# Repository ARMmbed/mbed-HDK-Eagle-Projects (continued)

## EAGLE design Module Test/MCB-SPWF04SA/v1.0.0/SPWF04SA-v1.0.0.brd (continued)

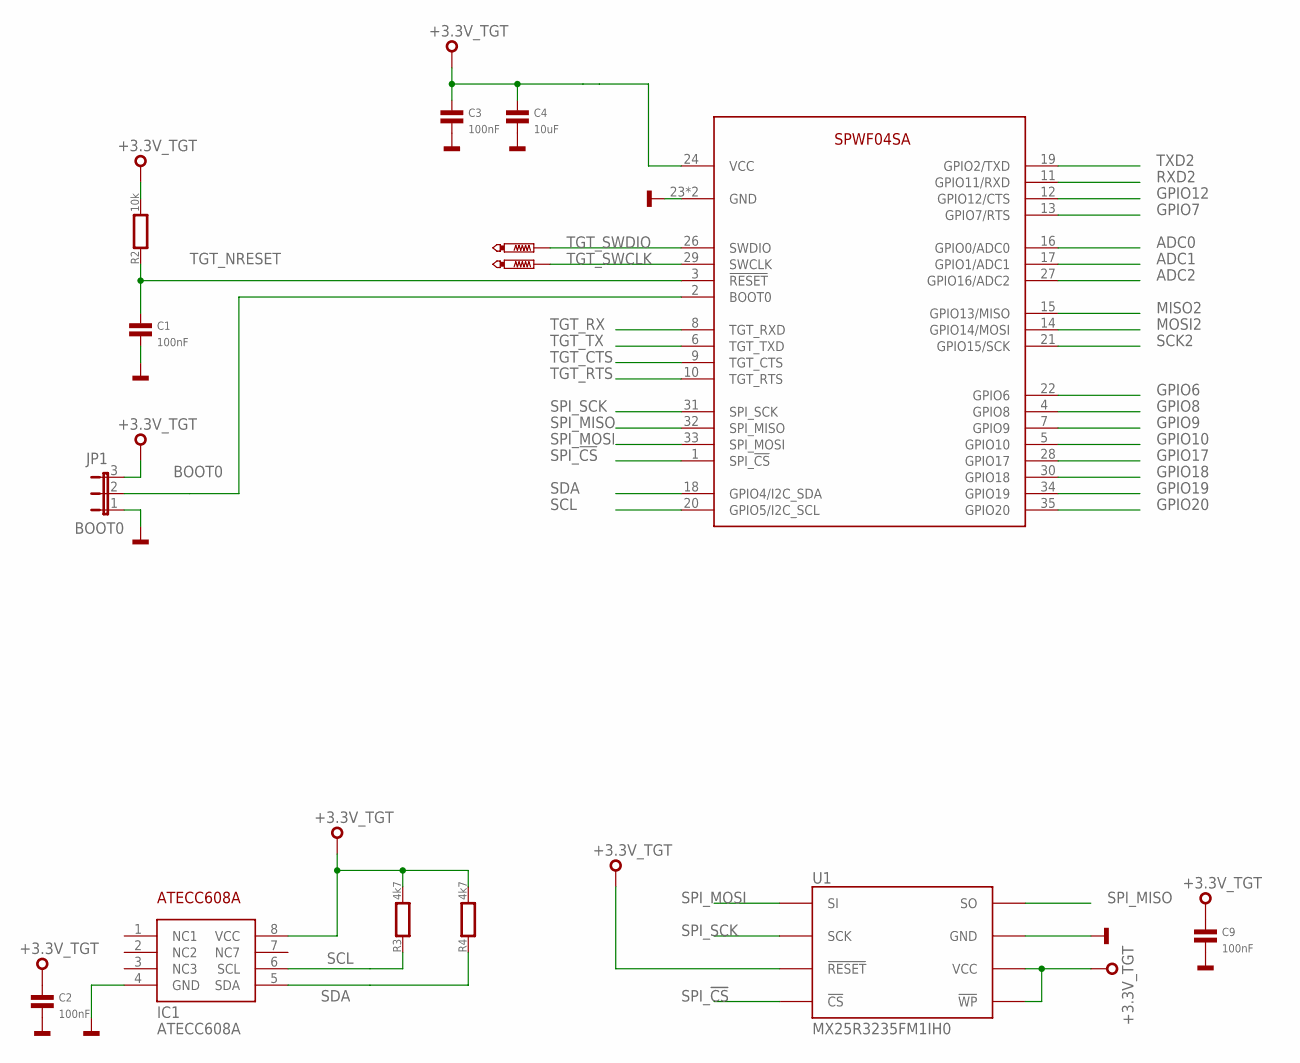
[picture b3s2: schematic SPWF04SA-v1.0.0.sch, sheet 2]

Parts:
C1, C2, C3, C9: 100nF; 0603
C4: 10uF; 0603
IC1: ATECC608A; SO8
JP1: BOOT0; JP2
MOD2: SPWF04SA
R2: 10k; 0603
R3, R4: 4k7; 0603
TP3, TP4: PTR1TP10R; TP10R
U1: MX25R3235FM1IH0; SO8

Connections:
+3.3V_TGT: C2.1, C3.1, C4.1, C9.1, IC1.8 (VCC), JP1.3, MOD2.24 (VCC), R2.2, R3.2, R4.2, U1.3 (!WP), U1.7 (!RESET), U1.8 (VCC); also elsewhere on the board
ADC0: MOD2.16 (GPIO0/ADC0); also elsewhere on the board
ADC1: MOD2.17 (GPIO1/ADC1); also elsewhere on the board
ADC2: MOD2.27 (GPIO16/ADC2); also elsewhere on the board
BOOT0: JP1.2, MOD2.2 (BOOT0)
GND: C1.2, C2.2, C3.2, C4.2, C9.2, IC1.4 (GND), JP1.1, MOD2.23 (GND), MOD2.25 (GND), U1.4 (GND); also elsewhere on the board
GPIO6: MOD2.22 (GPIO6); also elsewhere on the board
GPIO7: MOD2.13 (GPIO7/RTS); also elsewhere on the board
GPIO8: MOD2.4 (GPIO8); also elsewhere on the board
GPIO9: MOD2.7 (GPIO9); also elsewhere on the board
GPIO10: MOD2.5 (GPIO10)
GPIO12: MOD2.12 (GPIO12/CTS); also elsewhere on the board
GPIO17: MOD2.28 (GPIO17)
GPIO18: MOD2.30 (GPIO18); also elsewhere on the board
GPIO19: MOD2.34 (GPIO19)
GPIO20: MOD2.35 (GPIO20); also elsewhere on the board
MISO2: MOD2.15 (GPIO13/MISO); also elsewhere on the board
MOSI2: MOD2.14 (GPIO14/MOSI); also elsewhere on the board
RXD2: MOD2.11 (GPIO11/RXD); also elsewhere on the board
SCK2: MOD2.21 (GPIO15/SCK); also elsewhere on the board
SCL: IC1.6 (SCL), MOD2.20 (GPIO5/I2C_SCL), R3.1; also elsewhere on the board
SDA: IC1.5 (SDA), MOD2.18 (GPIO4/I2C_SDA), R4.1; also elsewhere on the board
SPI_!CS: MOD2.1 (SPI_!CS), U1.1 (!CS)
SPI_MISO: MOD2.32 (SPI_MISO), U1.2 (SO); also elsewhere on the board
SPI_MOSI: MOD2.33 (SPI_MOSI), U1.5 (SI); also elsewhere on the board
SPI_SCK: MOD2.31 (SPI_SCK), U1.6 (SCK); also elsewhere on the board
TGT_CTS: MOD2.9 (TGT_CTS); also elsewhere on the board
TGT_NRESET: C1.1, MOD2.3 (!RESET), R2.1; also elsewhere on the board
TGT_RTS: MOD2.10 (TGT_RTS); also elsewhere on the board
TGT_RX: MOD2.8 (TGT_RXD); also elsewhere on the board
TGT_SWCLK: MOD2.29 (SWCLK), TP4.TP; also elsewhere on the board
TGT_SWDIO: MOD2.26 (SWDIO), TP3.TP; also elsewhere on the board
TGT_TX: MOD2.6 (TGT_TXD); also elsewhere on the board
TXD2: MOD2.19 (GPIO2/TXD); also elsewhere on the board

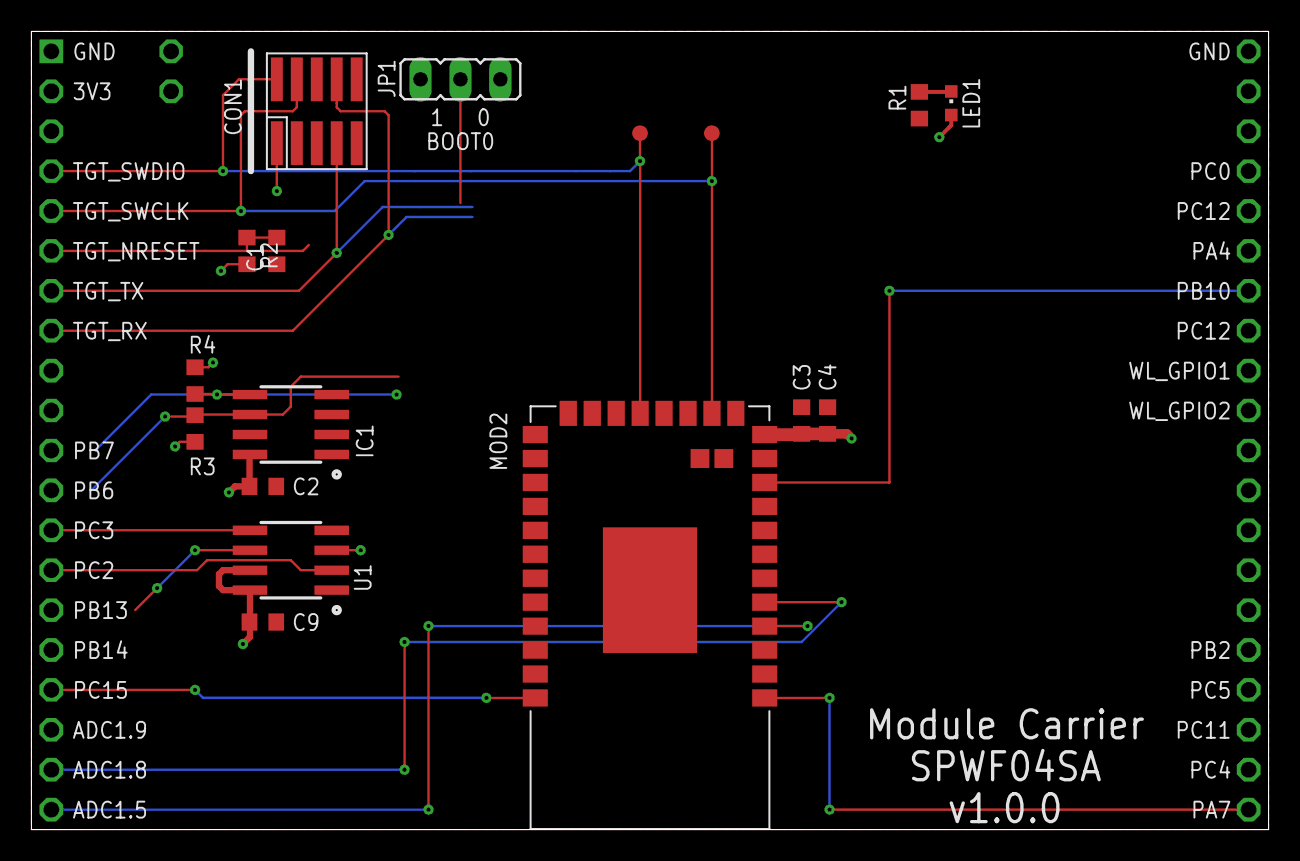
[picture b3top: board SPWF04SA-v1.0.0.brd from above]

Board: 2 copper layers, 78.7 x 50.8 mm, 21 parts (0 on the bottom side), 32 nets.

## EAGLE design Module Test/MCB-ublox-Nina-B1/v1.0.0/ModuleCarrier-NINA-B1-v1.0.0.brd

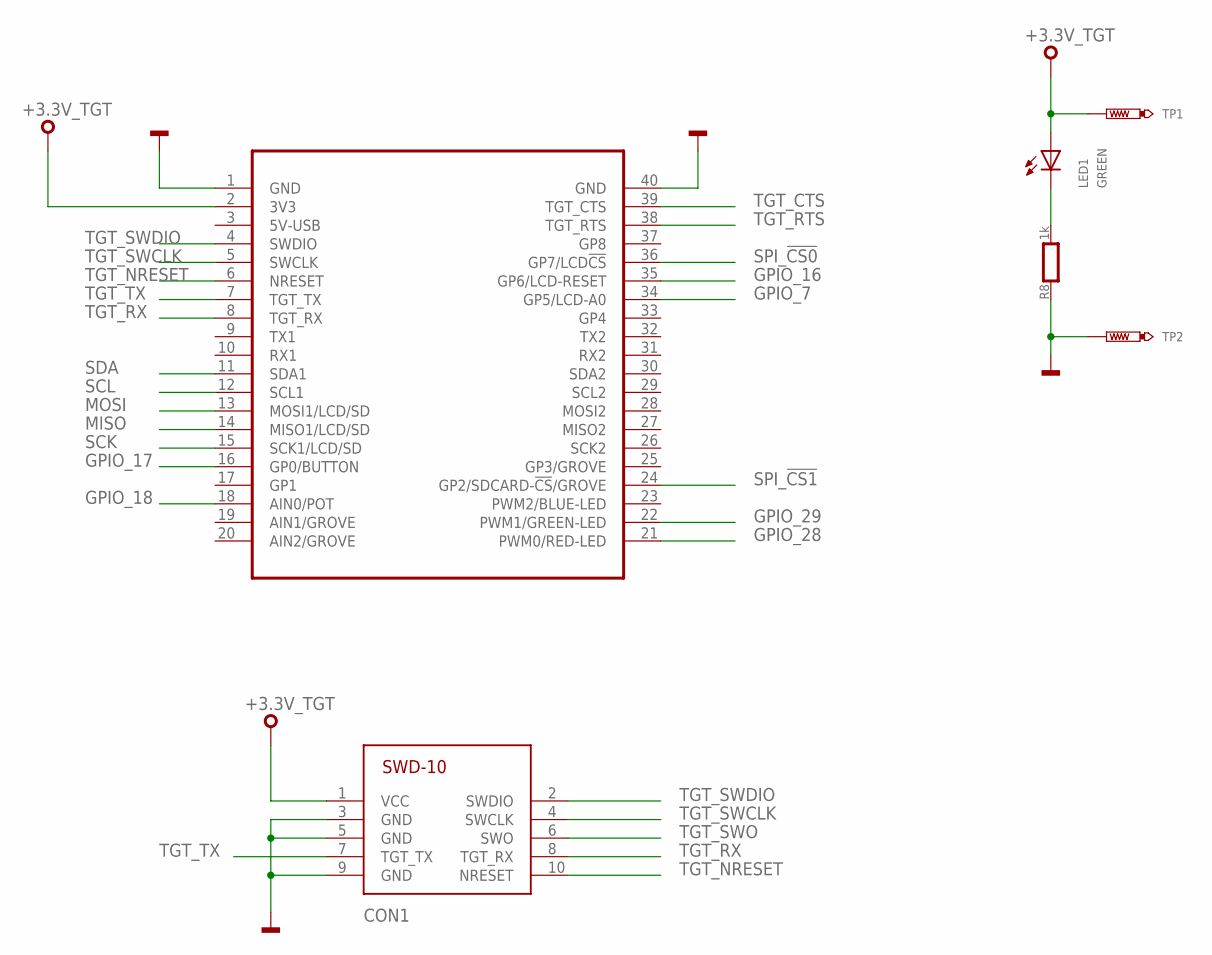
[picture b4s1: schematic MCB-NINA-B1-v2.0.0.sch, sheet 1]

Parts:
CON1: SWD-10/TC2050_SMD; FTSH-105-02
LED1: GREEN; CHIPLED_0603
MOD1: MODULE_DAUGHTER
R8: 1k; 0603
TP1, TP2: TEST-POINT-50R-PTH; TP50-PTH

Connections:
+3.3V_TGT: CON1.1 (VCC), LED1.A, MOD1.2 (3V3), TP1.TP; also elsewhere on the board
GND: CON1.3 (GND), CON1.5 (GND), CON1.9 (GND), MOD1.1 (GND), MOD1.40 (GND), R8.1, TP2.TP; also elsewhere on the board
GPIO_7: MOD1.34 (GP5/LCD-A0); also elsewhere on the board
GPIO_16: MOD1.35 (GP6/LCD-RESET); also elsewhere on the board
GPIO_17: MOD1.16 (GP0/BUTTON); also elsewhere on the board
GPIO_18: MOD1.18 (AIN0/POT); also elsewhere on the board
GPIO_28: MOD1.21 (PWM0/RED-LED); also elsewhere on the board
GPIO_29: MOD1.22 (PWM1/GREEN-LED); also elsewhere on the board
MISO: MOD1.14 (MISO1/LCD/SD); also elsewhere on the board
MOSI: MOD1.13 (MOSI1/LCD/SD); also elsewhere on the board
PA_1: LED1.C, R8.2
SCK: MOD1.15 (SCK1/LCD/SD); also elsewhere on the board
SCL: MOD1.12 (SCL1); also elsewhere on the board
SDA: MOD1.11 (SDA1); also elsewhere on the board
SPI_!CS0: MOD1.36 (GP7/LCD!CS); also elsewhere on the board
SPI_!CS1: MOD1.24 (GP2/SDCARD-!CS!/GROVE); also elsewhere on the board
TGT_CTS: MOD1.39 (TGT_CTS); also elsewhere on the board
TGT_NRESET: CON1.10 (NRESET), MOD1.6 (NRESET); also elsewhere on the board
TGT_RTS: MOD1.38 (TGT_RTS); also elsewhere on the board
TGT_RX: CON1.8 (TGT_RX), MOD1.8 (TGT_RX); also elsewhere on the board
TGT_SWCLK: CON1.4 (SWCLK), MOD1.5 (SWCLK); also elsewhere on the board
TGT_SWDIO: CON1.2 (SWDIO), MOD1.4 (SWDIO); also elsewhere on the board
TGT_SWO: CON1.6 (SWO); also elsewhere on the board
TGT_TX: CON1.7 (TGT_TX), MOD1.7 (TGT_TX); also elsewhere on the board

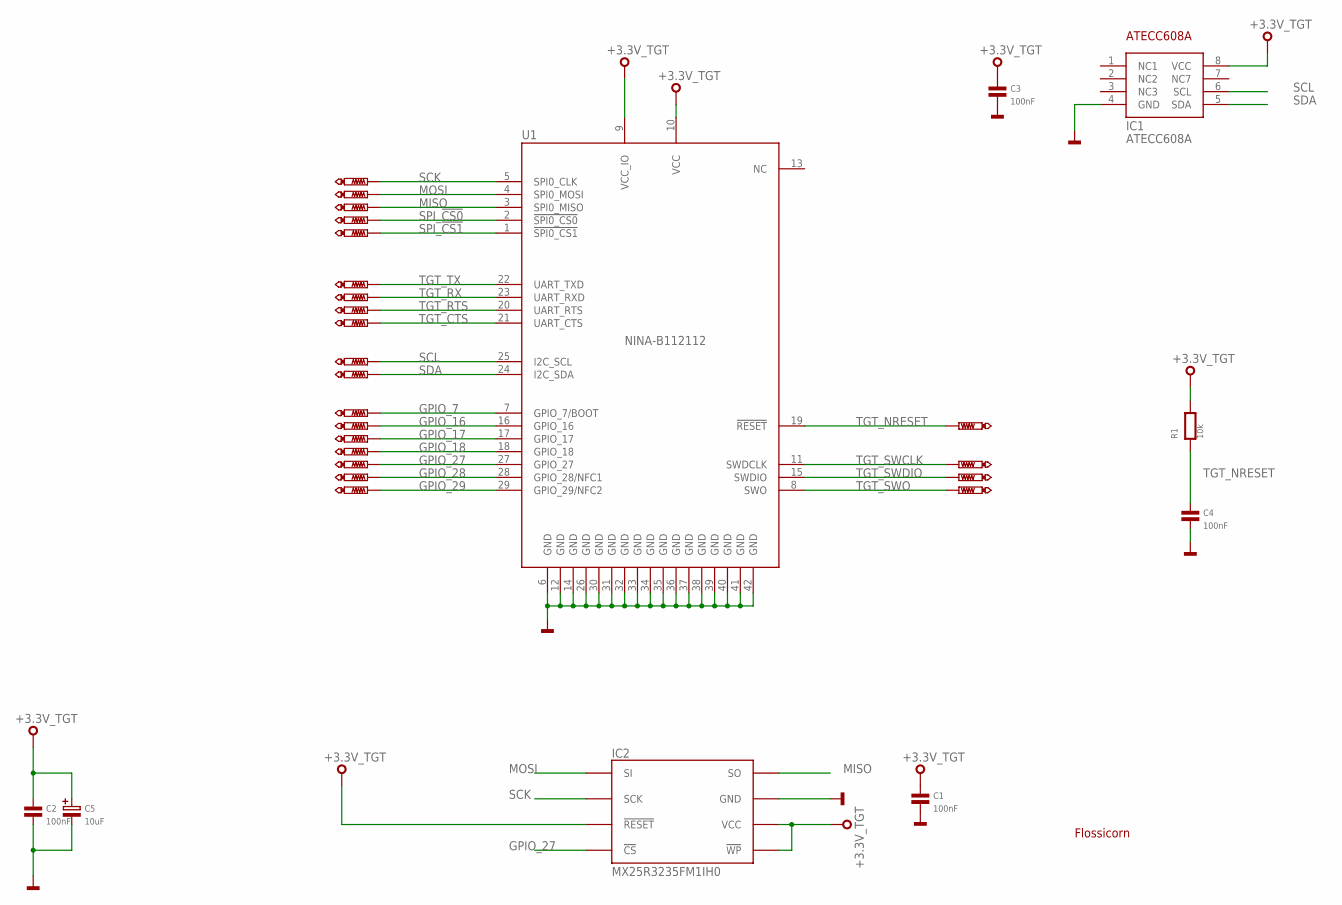
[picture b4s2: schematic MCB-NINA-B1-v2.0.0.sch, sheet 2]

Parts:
C1, C2, C3, C4: 100nF; 0603
C5: 10uF; SMC_B
IC1: ATECC608A; SO8
IC2: MX25R3235FM1IH0; SO8
R1: 10k; 0603
SS1: FLOSSICORN0.5; FLOSSICORN-0.5
TP3, TP4, TP5, TP6, TP7, TP8, TP9, TP10, TP11, TP12, TP13, TP14, TP15, TP16, TP17, TP18, TP19, TP20, TP21, TP22, TP23, TP24: PTR1B1,27; B1,27
U1: NINA-B112112; NINA112-42

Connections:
+3.3V_TGT: C1.1, C2.1, C3.1, C5.+, IC1.8 (VCC), IC2.3 (!WP), IC2.7 (!RESET), IC2.8 (VCC), R1.2, U1.9 (VCC_IO), U1.10 (VCC); also elsewhere on the board
GND: C1.2, C2.2, C3.2, C4.2, C5.-, IC1.4 (GND), IC2.4 (GND), U1.6 (GND), U1.12 (GND), U1.14 (GND), U1.26 (GND), U1.30 (GND), U1.31 (GND), U1.32 (GND), U1.33 (GND), U1.34 (GND), U1.35 (GND), U1.36 (GND), U1.37 (GND), U1.38 (GND), U1.39 (GND), U1.40 (GND), U1.41 (GND), U1.42 (GND); also elsewhere on the board
GPIO_7: TP14.TP, U1.7 (GPIO_7/BOOT); also elsewhere on the board
GPIO_16: TP15.TP, U1.16 (GPIO_16); also elsewhere on the board
GPIO_17: TP16.TP, U1.17 (GPIO_17); also elsewhere on the board
GPIO_18: TP17.TP, U1.18 (GPIO_18); also elsewhere on the board
GPIO_27: IC2.1 (!CS), TP18.TP, U1.27 (GPIO_27)
GPIO_28: TP19.TP, U1.28 (GPIO_28/NFC1); also elsewhere on the board
GPIO_29: TP20.TP, U1.29 (GPIO_29/NFC2); also elsewhere on the board
MISO: IC2.2 (SO), TP5.TP, U1.3 (SPI0_MISO); also elsewhere on the board
MOSI: IC2.5 (SI), TP4.TP, U1.4 (SPI0_MOSI); also elsewhere on the board
SCK: IC2.6 (SCK), TP3.TP, U1.5 (SPI0_CLK); also elsewhere on the board
SCL: IC1.6 (SCL), TP12.TP, U1.25 (I2C_SCL); also elsewhere on the board
SDA: IC1.5 (SDA), TP13.TP, U1.24 (I2C_SDA); also elsewhere on the board
SPI_!CS0: TP6.TP, U1.2 (!SPI0_CS0); also elsewhere on the board
SPI_!CS1: TP7.TP, U1.1 (!SPI0_CS1!); also elsewhere on the board
TGT_CTS: TP11.TP, U1.21 (UART_CTS); also elsewhere on the board
TGT_NRESET: C4.1, R1.1, TP21.TP, U1.19 (!RESET); also elsewhere on the board
TGT_RTS: TP10.TP, U1.20 (UART_RTS); also elsewhere on the board
TGT_RX: TP9.TP, U1.23 (UART_RXD); also elsewhere on the board
TGT_SWCLK: TP22.TP, U1.11 (SWDCLK); also elsewhere on the board
TGT_SWDIO: TP23.TP, U1.15 (SWDIO); also elsewhere on the board
TGT_SWO: TP24.TP, U1.8 (SWO); also elsewhere on the board
TGT_TX: TP8.TP, U1.22 (UART_TXD); also elsewhere on the board

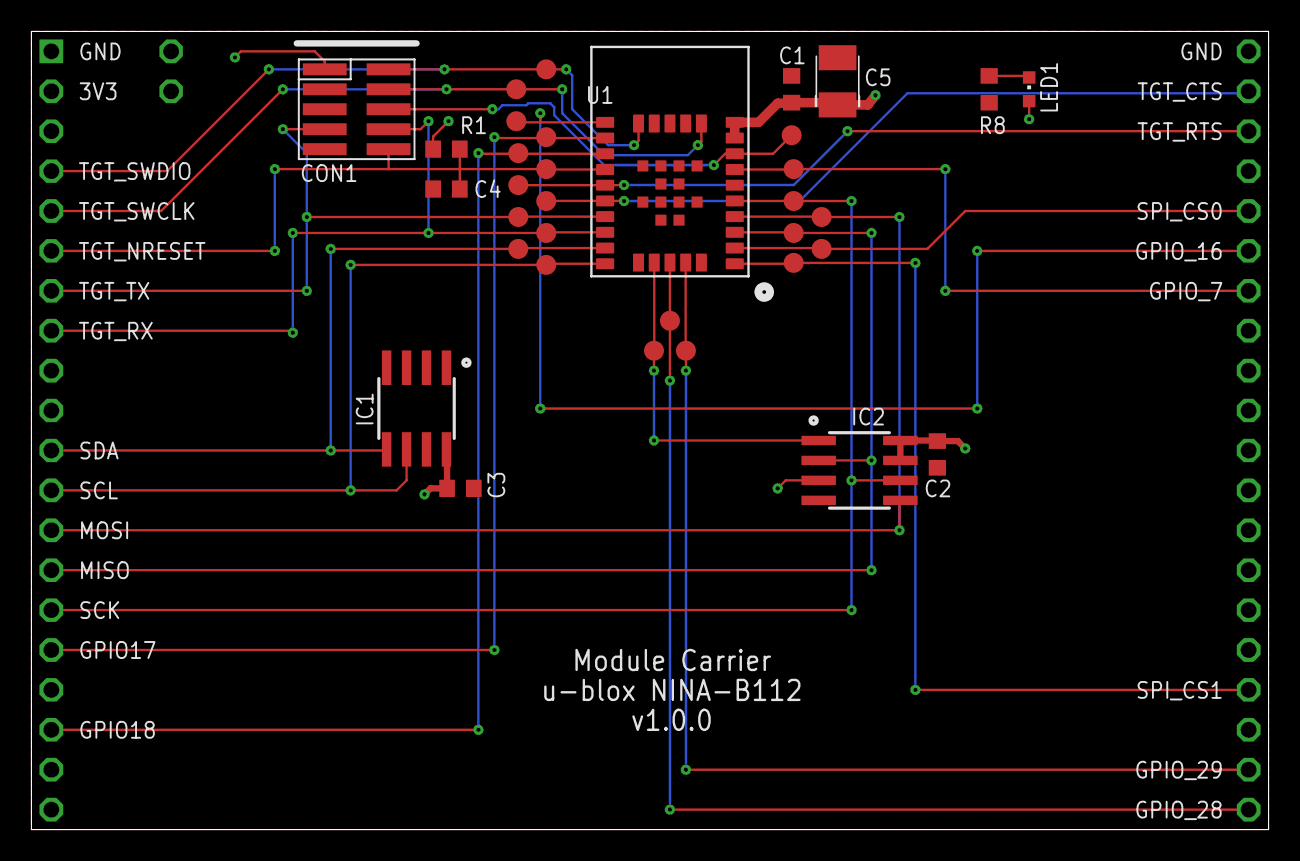
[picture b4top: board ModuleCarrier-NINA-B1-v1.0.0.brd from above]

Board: 2 copper layers, 78.7 x 50.8 mm, 37 parts (0 on the bottom side), 25 nets.

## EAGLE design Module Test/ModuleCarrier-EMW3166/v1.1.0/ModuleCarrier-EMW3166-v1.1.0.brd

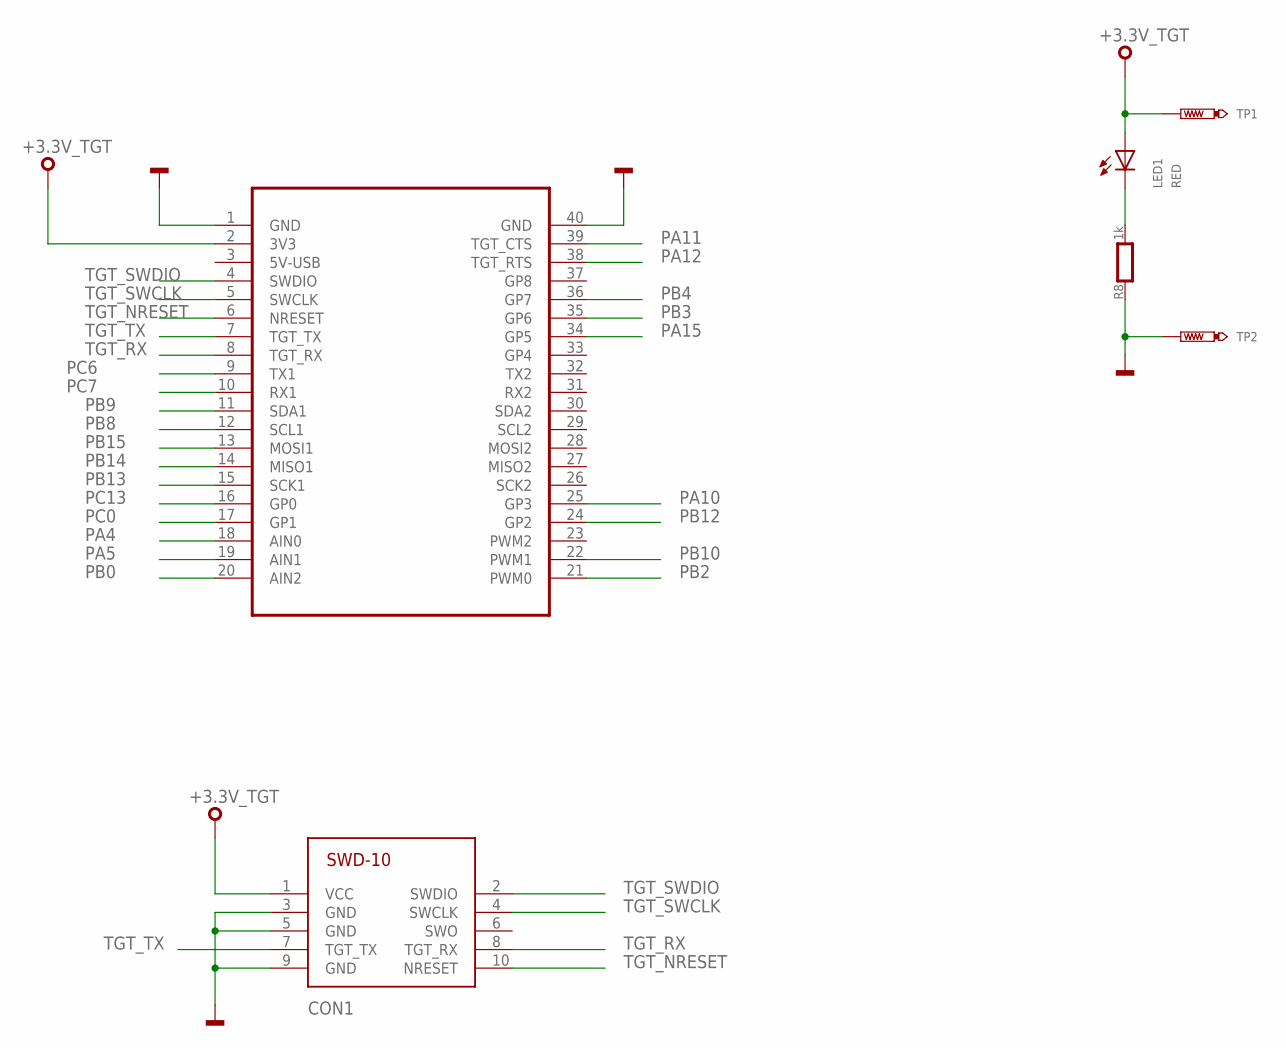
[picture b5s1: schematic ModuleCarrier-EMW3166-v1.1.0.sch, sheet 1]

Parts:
CON1: SWD-10/TC2050_SMD; FTSH-105-02
LED1: RED; CHIPLED_0603
R8: 1k; 0603
TP1, TP2: TEST-POINT-50R-PTH; TP50-PTH
U$1: MODULE_DAUGHTER

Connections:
+3.3V_TGT: CON1.1 (VCC), LED1.A, TP1.TP, U$1.2 (3V3); also elsewhere on the board
GND: CON1.3 (GND), CON1.5 (GND), CON1.9 (GND), R8.1, TP2.TP, U$1.1 (GND), U$1.40 (GND); also elsewhere on the board
PA4: U$1.18 (AIN0); also elsewhere on the board
PA5: U$1.19 (AIN1); also elsewhere on the board
PA10: U$1.25 (GP3); also elsewhere on the board
PA11: U$1.39 (TGT_CTS); also elsewhere on the board
PA12: U$1.38 (TGT_RTS); also elsewhere on the board
PA15: U$1.34 (GP5); also elsewhere on the board
PA_1: LED1.C, R8.2
PB0: U$1.20 (AIN2); also elsewhere on the board
PB2: U$1.21 (PWM0); also elsewhere on the board
PB3: U$1.35 (GP6); also elsewhere on the board
PB4: U$1.36 (GP7); also elsewhere on the board
PB8: U$1.12 (SCL1); also elsewhere on the board
PB9: U$1.11 (SDA1); also elsewhere on the board
PB10: U$1.22 (PWM1); also elsewhere on the board
PB12: U$1.24 (GP2); also elsewhere on the board
PB13: U$1.15 (SCK1); also elsewhere on the board
PB14: U$1.14 (MISO1); also elsewhere on the board
PB15: U$1.13 (MOSI1); also elsewhere on the board
PC0: U$1.17 (GP1); also elsewhere on the board
PC6: U$1.9 (TX1); also elsewhere on the board
PC7: U$1.10 (RX1); also elsewhere on the board
PC13: U$1.16 (GP0); also elsewhere on the board
TGT_NRESET: CON1.10 (NRESET), U$1.6 (NRESET); also elsewhere on the board
TGT_RX: CON1.8 (TGT_RX), U$1.8 (TGT_RX); also elsewhere on the board
TGT_SWCLK: CON1.4 (SWCLK), U$1.5 (SWCLK); also elsewhere on the board
TGT_SWDIO: CON1.2 (SWDIO), U$1.4 (SWDIO); also elsewhere on the board
TGT_TX: CON1.7 (TGT_TX), U$1.7 (TGT_TX); also elsewhere on the board

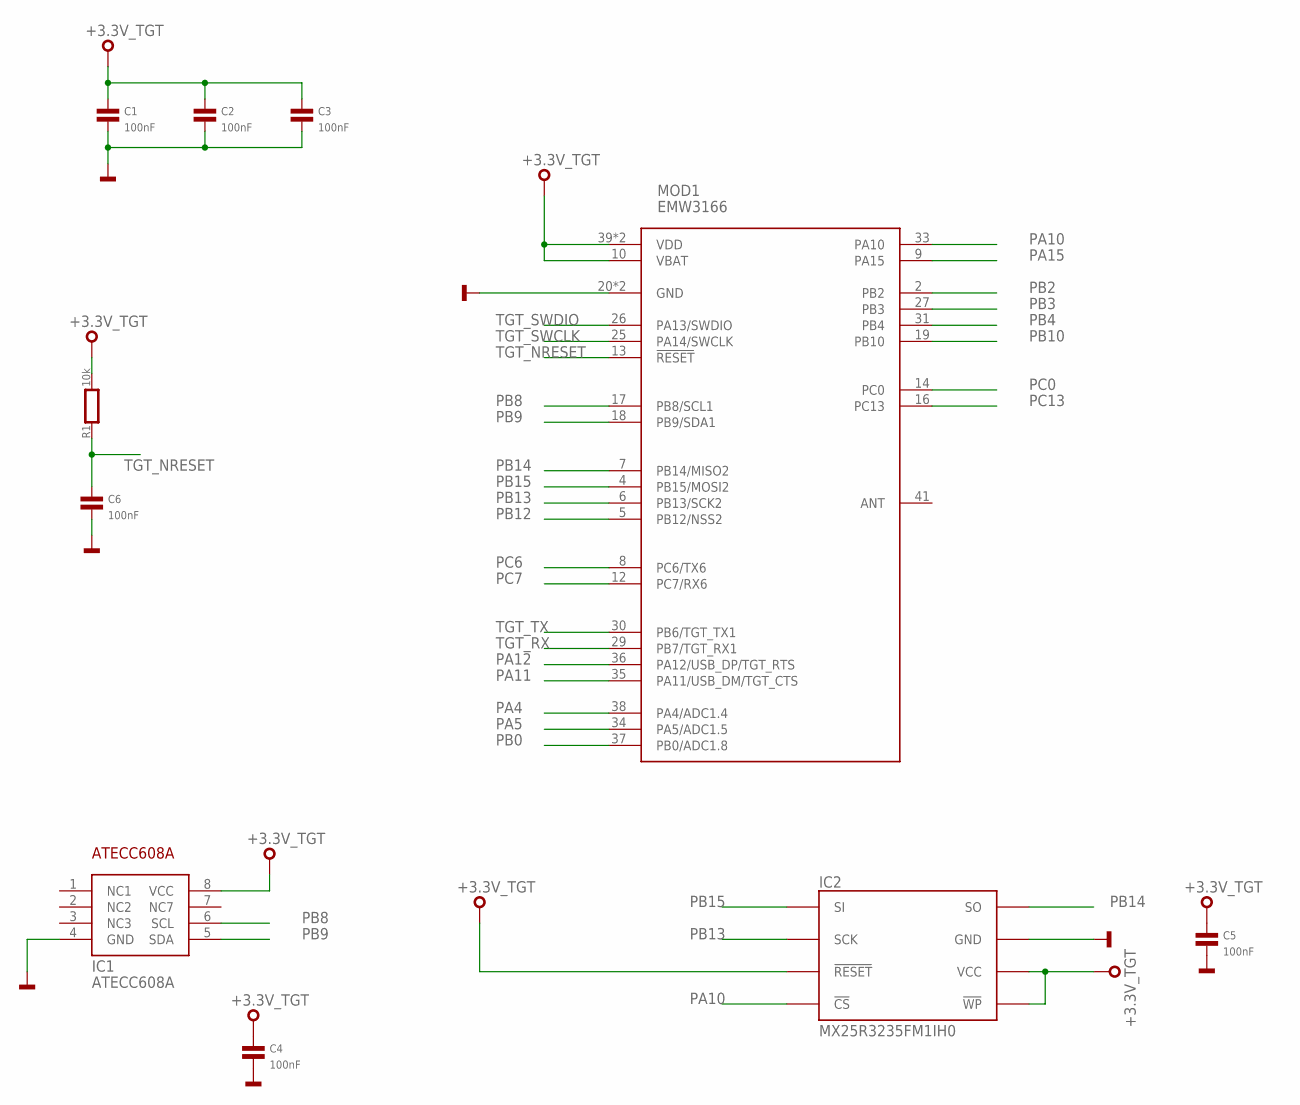
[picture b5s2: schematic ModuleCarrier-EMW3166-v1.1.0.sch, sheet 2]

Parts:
C1, C2, C3, C4, C5, C6: 100nF; 0603
IC1: ATECC608A; SO8
IC2: MX25R3235FM1IH0; SO8
MOD1: EMW3166
R1: 10k; 0603

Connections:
+3.3V_TGT: C1.1, C2.1, C3.1, C4.1, C5.1, IC1.8 (VCC), IC2.3 (!WP), IC2.7 (!RESET), IC2.8 (VCC), MOD1.10 (VBAT), MOD1.39 (VDD), MOD1.40 (VDD), R1.2; also elsewhere on the board
GND: C1.2, C2.2, C3.2, C4.2, C5.2, C6.2, IC1.4 (GND), IC2.4 (GND), MOD1.20 (GND), MOD1.21 (GND); also elsewhere on the board
PA4: MOD1.38 (PA4/ADC1.4); also elsewhere on the board
PA5: MOD1.34 (PA5/ADC1.5); also elsewhere on the board
PA10: IC2.1 (!CS), MOD1.33 (PA10); also elsewhere on the board
PA11: MOD1.35 (PA11/USB_DM/TGT_CTS); also elsewhere on the board
PA12: MOD1.36 (PA12/USB_DP/TGT_RTS); also elsewhere on the board
PA15: MOD1.9 (PA15); also elsewhere on the board
PB0: MOD1.37 (PB0/ADC1.8); also elsewhere on the board
PB2: MOD1.2 (PB2); also elsewhere on the board
PB3: MOD1.27 (PB3); also elsewhere on the board
PB4: MOD1.31 (PB4); also elsewhere on the board
PB8: IC1.6 (SCL), MOD1.17 (PB8/SCL1); also elsewhere on the board
PB9: IC1.5 (SDA), MOD1.18 (PB9/SDA1); also elsewhere on the board
PB10: MOD1.19 (PB10); also elsewhere on the board
PB12: MOD1.5 (PB12/NSS2); also elsewhere on the board
PB13: IC2.6 (SCK), MOD1.6 (PB13/SCK2); also elsewhere on the board
PB14: IC2.2 (SO), MOD1.7 (PB14/MISO2); also elsewhere on the board
PB15: IC2.5 (SI), MOD1.4 (PB15/MOSI2); also elsewhere on the board
PC0: MOD1.14 (PC0); also elsewhere on the board
PC6: MOD1.8 (PC6/TX6); also elsewhere on the board
PC7: MOD1.12 (PC7/RX6); also elsewhere on the board
PC13: MOD1.16 (PC13); also elsewhere on the board
TGT_NRESET: C6.1, MOD1.13 (!RESET), R1.1; also elsewhere on the board
TGT_RX: MOD1.29 (PB7/TGT_RX1); also elsewhere on the board
TGT_SWCLK: MOD1.25 (PA14/SWCLK); also elsewhere on the board
TGT_SWDIO: MOD1.26 (PA13/SWDIO); also elsewhere on the board
TGT_TX: MOD1.30 (PB6/TGT_TX1); also elsewhere on the board

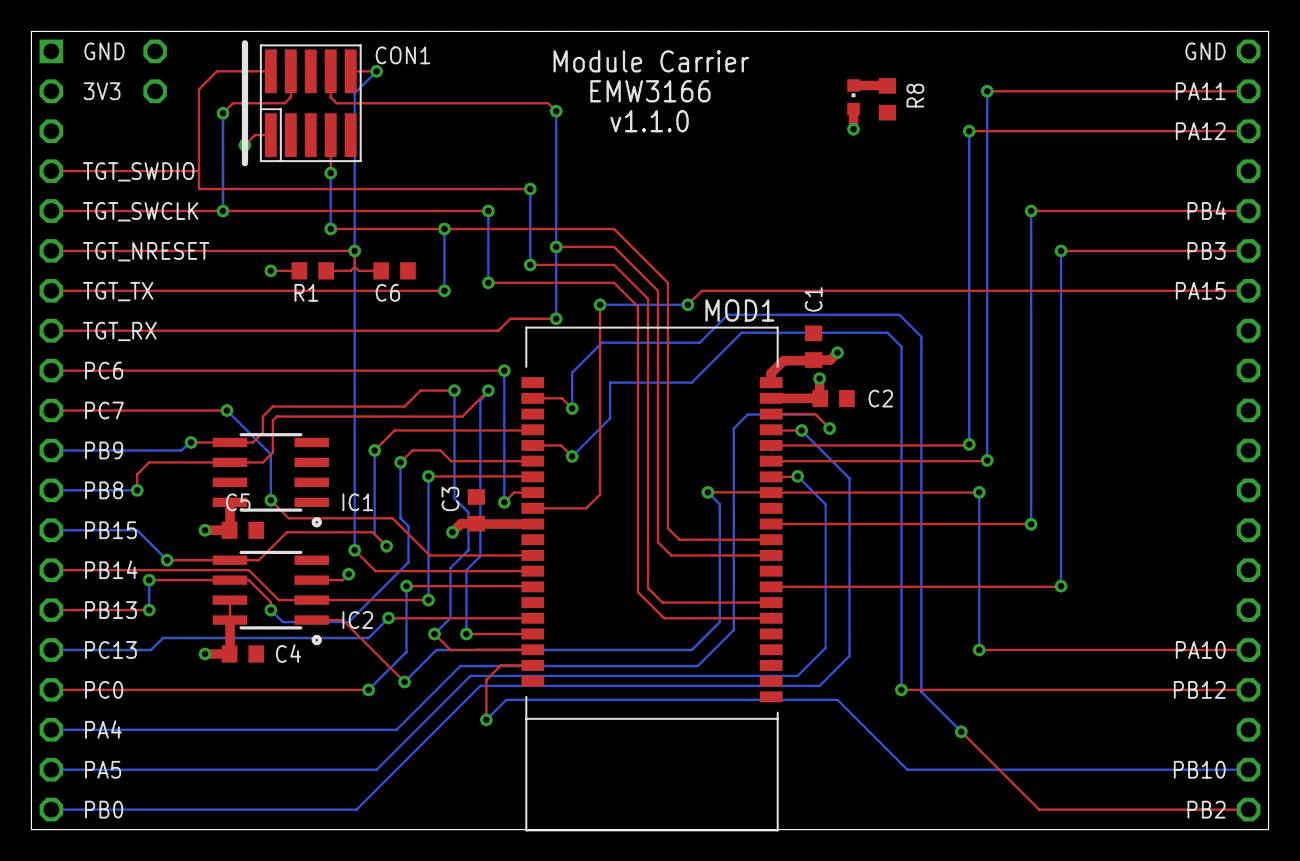
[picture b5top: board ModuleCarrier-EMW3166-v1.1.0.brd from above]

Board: 2 copper layers, 78.7 x 50.8 mm, 16 parts (0 on the bottom side), 29 nets.
